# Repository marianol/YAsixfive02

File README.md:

# YAsixfive02 - Yet another 6502 SBC

Just my own take on a 6502 single board computer, inspired on Garth Wilson's excellent 6502 Primer, Daryl Rictor, Ben Eater, and my own beautiful C=64 and all the classic 8-bit computers of the laste 70s early 80s
This repository contains all the work in progress while I build my own SBC. So far I only have my PCB work here, more to come. 
I got tired of having a rat's nest of wires in breadboards and since I'm no wire-rapper I started with a basic PCB to hold CPU, Memory and ROM with a connector so I can start testing the "extras" like serial, VIA, etc.

Not that this is work in progress.. 

## References and Credits

This is my list of references and places where I have found most of the answers to my questions:

- [Ben Eater](https://eater.net) - his videos inspired me to start playing with electronicas again.
- [Garth Wilson's 6502 Primer](http://wilsonminesco.com/6502primer/) - Kudos sir, you have created the bible of 6502-SBC information.
- [Daryl Rictor](https://sbc.rictor.org/home.html) - great documentation on his projects and infinite wisdom in the 6505.org forum.
- [Grant Searle](http://searle.x10host.com/6502/Simple6502.html) - Great example and information on his simple 8 (or 7) chip 6502 SBC.
- And of course 6502.org, Reddit and all the people that share information that I find with google :)

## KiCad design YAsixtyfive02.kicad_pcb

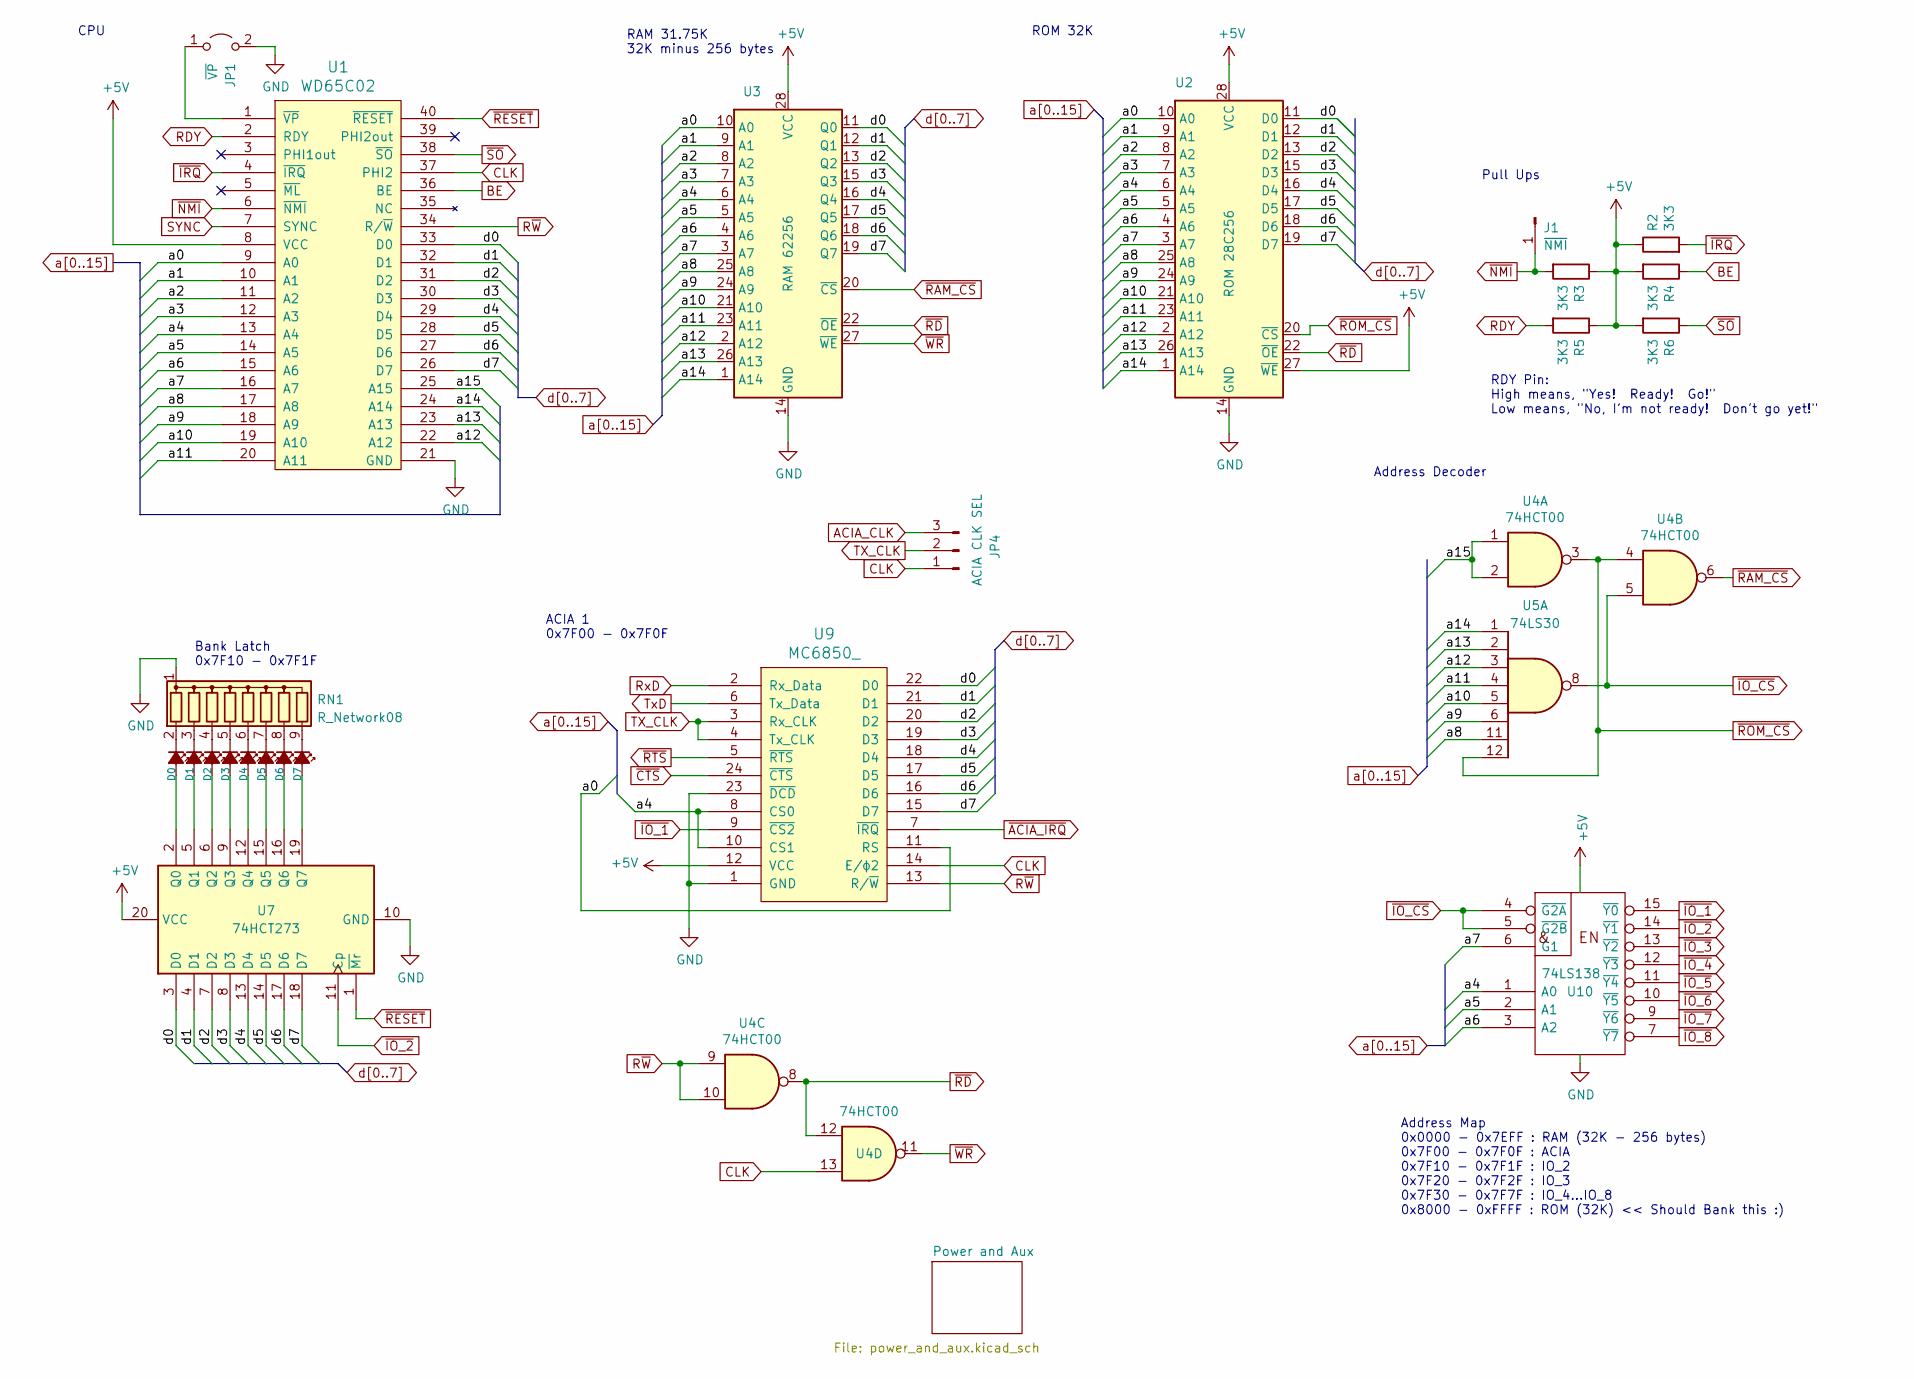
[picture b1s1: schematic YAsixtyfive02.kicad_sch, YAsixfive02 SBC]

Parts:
D0: CTL_0; LED_SMALL_3.0mm
D1: CTL_1; LED_SMALL_3.0mm
D2: CTL_2; LED_SMALL_3.0mm
D3, D4, D5, D6, D7: 3; LED_SMALL_3.0mm
J1: ~{NMI}; PinHeader_1x01_P2.54mm_Vertical
JP1: ~{VP}; PinHeader_1x02_P2.54mm_Vertical
JP4: ACIA CLK SEL; PinHeader_1x03_P2.54mm_Vertical
R2, R3, R4, R5, R6: 3K3; R_Axial_DIN0207_L6.3mm_D2.5mm_P10.16mm_Horizontal
RN1: R_Network08; R_Array_SIP9
U1: WD65C02; DIP-40_W15.24mm_Socket_LongPads
U2: ROM 28C256; DIP-28_W15.24mm_Socket_LongPads
U3: RAM 62256; DIP-28_W15.24mm_Socket_LongPads
U4: 74HCT00; DIP-14_W7.62mm_Socket_LongPads
U5: 74LS30; DIP-14_W7.62mm_Socket_LongPads
U7: 74HCT273; DIP-20_W7.62mm_Socket_LongPads
U9: MC6850_; DIP-24_W15.24mm_Socket_LongPads
U10: 74LS138; DIP-16_W7.62mm_Socket_LongPads

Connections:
+5V: R2.1, R3.1, R4.2, R5.1, R6.2, U1.8 (VCC), U2.27 (~WE), U2.28 (VCC), U3.28 (VCC), U7.20 (VCC), U9.12 (VCC), U10.16 (VCC); also elsewhere on the board
ACIA_CLK: JP4.3
BE: R4.1, U1.36 (BE)
CLK: JP4.1, U1.37 (PHI2), U4.13, U9.14 (E/ϕ2); also elsewhere on the board
GND: JP1.2 (B), RN1.1 (common), U1.21 (GND), U2.14 (GND), U3.14 (GND), U7.10 (GND), U9.1 (GND), U9.23 (~DCD), U10.8 (GND); also elsewhere on the board
unnamed: D0.1 (K), RN1.2 (R1)
unnamed: D0.2 (A), U7.2 (Q0)
unnamed: D1.1 (K), RN1.3 (R2)
unnamed: D1.2 (A), U7.5 (Q1)
unnamed: D2.1 (K), RN1.4 (R3)
unnamed: D2.2 (A), U7.6 (Q2)
unnamed: D3.1 (K), RN1.5 (R4)
unnamed: D3.2 (A), U7.9 (Q3)
unnamed: D4.1 (K), RN1.6 (R5)
unnamed: D4.2 (A), U7.12 (Q4)
unnamed: D5.1 (K), RN1.7 (R6)
unnamed: D5.2 (A), U7.15 (Q5)
unnamed: D6.1 (K), RN1.8 (R7)
unnamed: D6.2 (A), U7.16 (Q6)
unnamed: D7.1 (K), RN1.9 (R8)
unnamed: D7.2 (A), U7.19 (Q7)
unnamed: JP1.1 (A), U1.1 (~VP)
RDY: R5.2, U1.2 (RDY); also elsewhere on the board
RxD: U9.2 (Rx_Data); also elsewhere on the board
R~W: U1.34 (R/~W), U4.9, U4.10, U9.13 (R/~W); also elsewhere on the board
SYNC: U1.7 (SYNC); also elsewhere on the board
TX_CLK: JP4.2, U9.3 (Rx_CLK), U9.4 (Tx_CLK); also elsewhere on the board
TxD: U9.6 (Tx_Data); also elsewhere on the board
a0: U1.9 (A0), U2.10 (A0), U3.10 (A0), U9.11 (RS); also elsewhere on the board
a1: U1.10 (A1), U2.9 (A1), U3.9 (A1); also elsewhere on the board
a2: U1.11 (A2), U2.8 (A2), U3.8 (A2); also elsewhere on the board
a3: U1.12 (A3), U2.7 (A3), U3.7 (A3); also elsewhere on the board
a4: U1.13 (A4), U2.6 (A4), U3.6 (A4), U9.8 (CS0), U9.10 (CS1), U10.1 (A0); also elsewhere on the board
a5: U1.14 (A5), U2.5 (A5), U3.5 (A5), U10.2 (A1); also elsewhere on the board
a6: U1.15 (A6), U2.4 (A6), U3.4 (A6), U10.3 (A2); also elsewhere on the board
a7: U1.16 (A7), U2.3 (A7), U3.3 (A7), U10.6 (G1); also elsewhere on the board
a8: U1.17 (A8), U2.25 (A8), U3.25 (A8), U5.11; also elsewhere on the board
a9: U1.18 (A9), U2.24 (A9), U3.24 (A9), U5.6; also elsewhere on the board
a10: U1.19 (A10), U2.21 (A10), U3.21 (A10), U5.5; also elsewhere on the board
a11: U1.20 (A11), U2.23 (A11), U3.23 (A11), U5.4; also elsewhere on the board
a12: U1.22 (A12), U2.2 (A12), U3.2 (A12), U5.3; also elsewhere on the board
a13: U1.23 (A13), U2.26 (A13), U3.26 (A13), U5.2; also elsewhere on the board
a14: U1.24 (A14), U2.1 (A14), U3.1 (A14), U5.1; also elsewhere on the board
a15: U1.25 (A15), U4.1, U4.2; also elsewhere on the board
d0: U1.33 (D0), U2.11 (D0), U3.11 (Q0), U7.3 (D0), U9.22 (D0); also elsewhere on the board
d1: U1.32 (D1), U2.12 (D1), U3.12 (Q1), U7.4 (D1), U9.21 (D1); also elsewhere on the board
d2: U1.31 (D2), U2.13 (D2), U3.13 (Q2), U7.7 (D2), U9.20 (D2); also elsewhere on the board
d3: U1.30 (D3), U2.15 (D3), U3.15 (Q3), U7.8 (D3), U9.19 (D3); also elsewhere on the board
d4: U1.29 (D4), U2.16 (D4), U3.16 (Q4), U7.13 (D4), U9.18 (D4); also elsewhere on the board
d5: U1.28 (D5), U2.17 (D5), U3.17 (Q5), U7.14 (D5), U9.17 (D5); also elsewhere on the board
d6: U1.27 (D6), U2.18 (D6), U3.18 (Q6), U7.17 (D6), U9.16 (D6); also elsewhere on the board
d7: U1.26 (D7), U2.19 (D7), U3.19 (Q7), U7.18 (D7), U9.15 (D7); also elsewhere on the board
~ACIA_IRQ: U9.7 (~IRQ); also elsewhere on the board
~CTS: U9.24 (~CTS); also elsewhere on the board
~IO_1: U9.9 (~CS2), U10.15 (~Y0)
~IO_2: U7.11 (Cp), U10.14 (~Y1)
~IO_3: U10.13 (~Y2); also elsewhere on the board
~IO_4: U10.12 (~Y3); also elsewhere on the board
~IO_5: U10.11 (~Y4); also elsewhere on the board
~IO_6: U10.10 (~Y5); also elsewhere on the board
~IO_7: U10.9 (~Y6); also elsewhere on the board
~IO_8: U10.7 (~Y7); also elsewhere on the board
~IO_CS: U4.5, U5.8, U10.4 (~G2A), U10.5 (~G2B); also elsewhere on the board
~IRQ: R2.2, U1.4 (~IRQ); also elsewhere on the board
~NMI: J1.1, R3.2, U1.6 (~NMI); also elsewhere on the board
~RAM_CS: U3.20 (~CS), U4.6; also elsewhere on the board
~RD: U2.22 (~OE), U3.22 (~OE), U4.8, U4.12; also elsewhere on the board
~RESET: U1.40 (~RESET), U7.1 (~Mr); also elsewhere on the board
~ROM_CS: U2.20 (~CS), U4.3, U4.4, U5.12; also elsewhere on the board
~RTS: U9.5 (~RTS); also elsewhere on the board
~SO: R6.1, U1.38 (~SO)
~WR: U3.27 (~WE), U4.11; also elsewhere on the board

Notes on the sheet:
CPU
Pull Ups
ROM 32K
RDY Pin: High means, "Yes! Ready! Go!" Low means, "No, I'm not ready! Don't go yet!"
Address Decoder
RAM 31.75K 32K minus 256 bytes
Bank Latch 0x7F10 - 0x7F1F
ACIA 1 0x7F00 - 0x7F0F
Address Map 0x0000 - 0x7EFF : RAM (32K - 256 bytes) 0x7F00 - 0x7F0F : ACIA 0x7F10 - 0x7F1F : IO_2 0x7F20 - 0x7F2F : IO_3 0x7F30 - 0x7F7F : IO_4...IO_8 0x8000 - 0xFFFF : ROM (32K) << Should Bank this :)

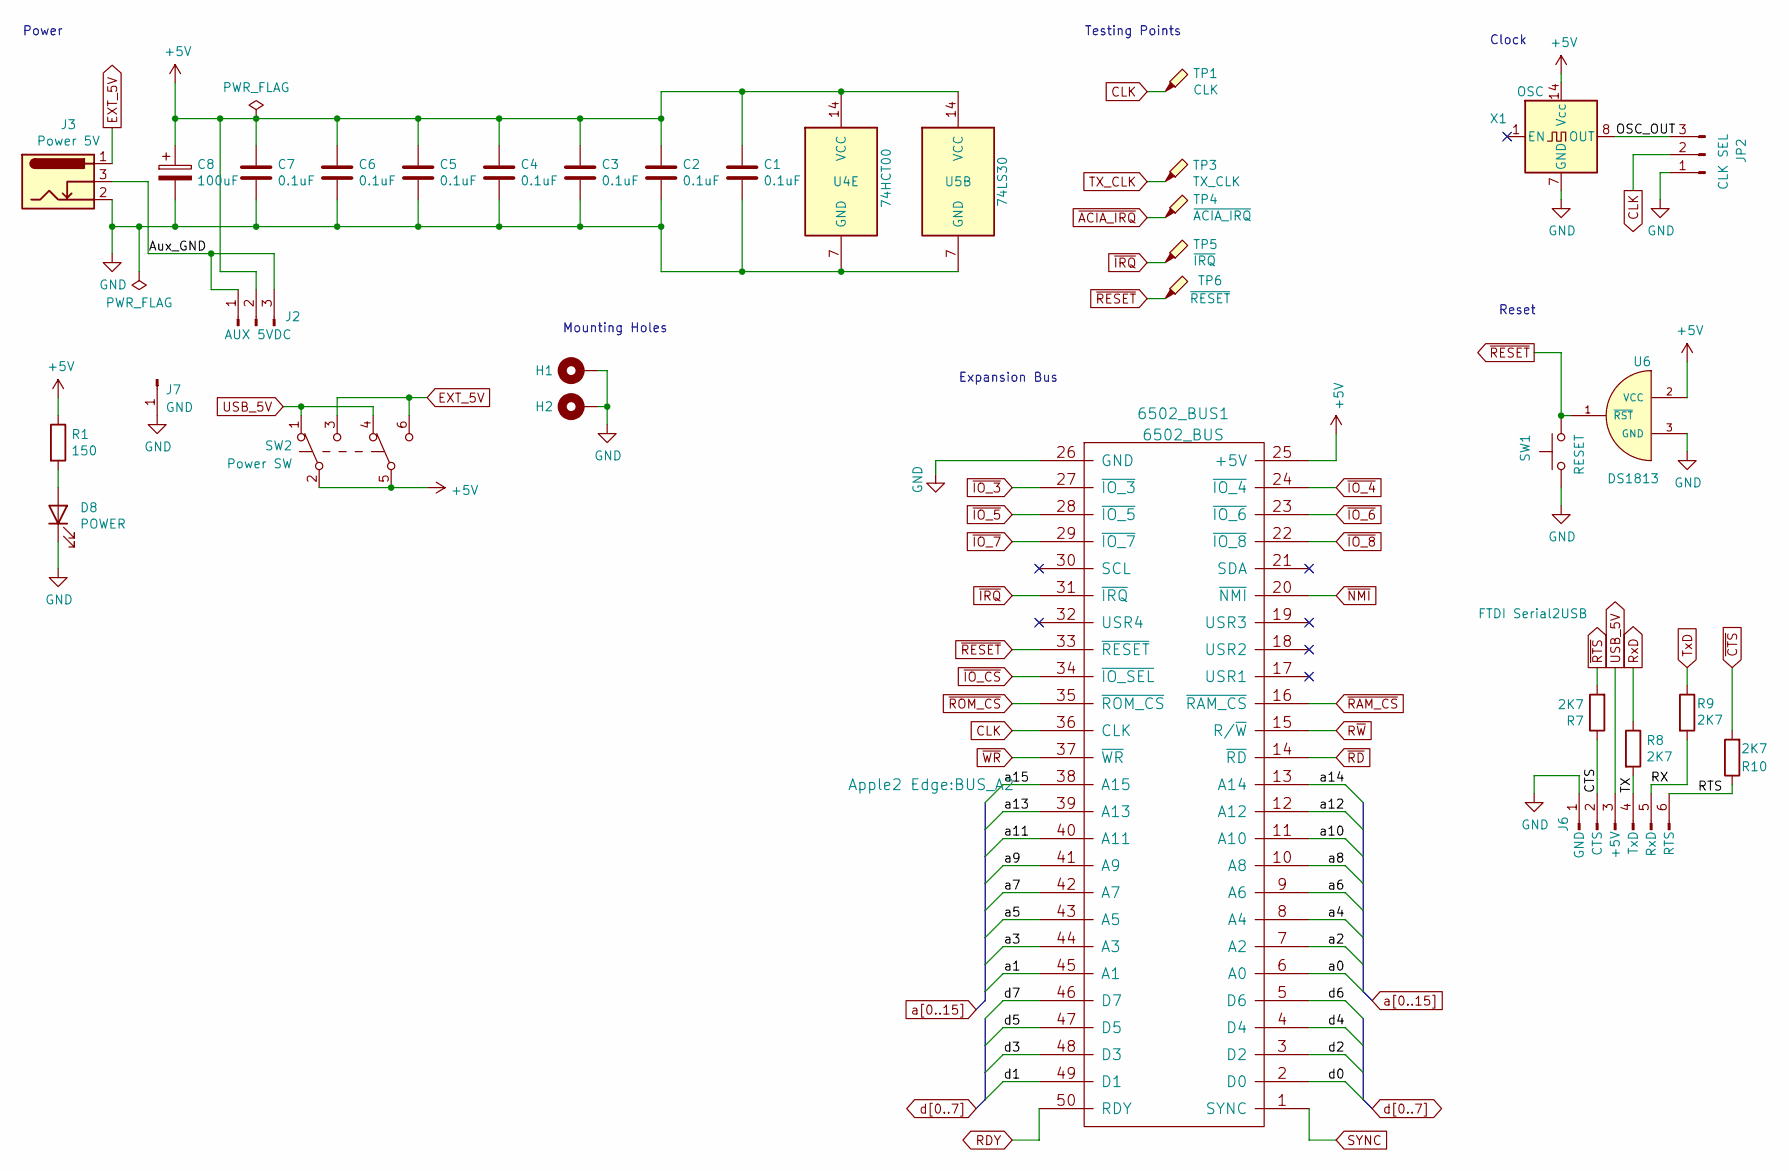
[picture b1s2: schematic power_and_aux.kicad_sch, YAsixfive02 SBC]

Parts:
6502_BUS1: 6502_BUS; BUS_A2
C1, C2, C3, C4, C5, C6, C7: 0.1uF; C_Disc_D4.3mm_W1.9mm_P5.00mm
C8: 100uF; CP_Radial_D6.3mm_P2.50mm
D8: POWER; LED_D3.0mm
H1, H2: MNT; MountingHole_3.2mm_M3_DIN965_Pad_TopBottom
J2: AUX 5VDC; PinHeader_1x03_P2.54mm_Vertical
J3: Power 5V; BarrelJack_Horizontal
J6: FTDI Serial2USB; PinHeader_1x06_P2.54mm_Vertical
J7: GND; PinHeader_1x01_P2.54mm_Vertical
JP2: CLK SEL; PinHeader_1x03_P2.54mm_Vertical
R1: 150; R_Axial_DIN0207_L6.3mm_D2.5mm_P10.16mm_Horizontal
R7, R8, R9, R10: 2K7; R_Axial_DIN0207_L6.3mm_D2.5mm_P10.16mm_Horizontal
SW1: RESET; SW_PUSH_6mm_H5mm
SW2: Power SW; SW_NKK_GW12LJP
TP1: CLK; TestPoint_THTPad_1.0x1.0mm_Drill0.5mm
TP3: TX_CLK; TestPoint_THTPad_1.0x1.0mm_Drill0.5mm
TP4: ~{ACIA_IRQ}; TestPoint_THTPad_1.0x1.0mm_Drill0.5mm
TP5: ~{IRQ}; TestPoint_THTPad_1.0x1.0mm_Drill0.5mm
TP6: ~{RESET}; TestPoint_THTPad_1.0x1.0mm_Drill0.5mm
U4: 74HCT00; DIP-14_W7.62mm_Socket_LongPads
U5: 74LS30; DIP-14_W7.62mm_Socket_LongPads
U6: DS1813; TO-92; MANUFACTURER_PART_NUMBER ds181315+
X1: OSC; Oscillator_DIP-14

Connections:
+5V: 6502_BUS1.25 (+5V), C1.1, C2.1, C3.1, C4.1, C5.1, C6.1, C7.1, C8.1, J2.2, R1.1, SW2.2 (B), SW2.5 (B), U4.14 (VCC), U5.14 (VCC), U6.2 (VCC), X1.14 (Vcc); also elsewhere on the board
/Power and Aux/Aux_GND: J2.1, J2.3, J3.3
/Power and Aux/CTS: J6.2 (CTS), R7.1
/Power and Aux/OSC_OUT: JP2.3, X1.8 (OUT)
/Power and Aux/RTS: J6.6 (RTS), R10.1
/Power and Aux/RX: J6.5 (RxD), R9.2
/Power and Aux/TX: J6.4 (TxD), R8.2
CLK: 6502_BUS1.36 (CLK), JP2.2, TP1.1; also elsewhere on the board
EXT_5V: J3.1, SW2.3 (C), SW2.6 (C)
GND: 6502_BUS1.26 (GND), C1.2, C2.2, C3.2, C4.2, C5.2, C6.2, C7.2, C8.2, D8.1 (K), H1.1, H2.1, J3.2, J6.1 (GND), J7.1, JP2.1, SW1.1, U4.7 (GND), U5.7 (GND), U6.3 (GND), X1.7 (GND); also elsewhere on the board
unnamed: D8.2 (A), R1.2
RDY: 6502_BUS1.50 (RDY); also elsewhere on the board
RxD: R8.1; also elsewhere on the board
R~W: 6502_BUS1.15 (R/~W); also elsewhere on the board
SYNC: 6502_BUS1.1 (SYNC); also elsewhere on the board
TX_CLK: TP3.1; also elsewhere on the board
TxD: R9.1; also elsewhere on the board
USB_5V: J6.3 (+5V), SW2.1 (A), SW2.4 (A)
a0: 6502_BUS1.6 (A0); also elsewhere on the board
a1: 6502_BUS1.45 (A1); also elsewhere on the board
a2: 6502_BUS1.7 (A2); also elsewhere on the board
a3: 6502_BUS1.44 (A3); also elsewhere on the board
a4: 6502_BUS1.8 (A4); also elsewhere on the board
a5: 6502_BUS1.43 (A5); also elsewhere on the board
a6: 6502_BUS1.9 (A6); also elsewhere on the board
a7: 6502_BUS1.42 (A7); also elsewhere on the board
a8: 6502_BUS1.10 (A8); also elsewhere on the board
a9: 6502_BUS1.41 (A9); also elsewhere on the board
a10: 6502_BUS1.11 (A10); also elsewhere on the board
a11: 6502_BUS1.40 (A11); also elsewhere on the board
a12: 6502_BUS1.12 (A12); also elsewhere on the board
a13: 6502_BUS1.39 (A13); also elsewhere on the board
a14: 6502_BUS1.13 (A14); also elsewhere on the board
a15: 6502_BUS1.38 (A15); also elsewhere on the board
d0: 6502_BUS1.2 (D0); also elsewhere on the board
d1: 6502_BUS1.49 (D1); also elsewhere on the board
d2: 6502_BUS1.3 (D2); also elsewhere on the board
d3: 6502_BUS1.48 (D3); also elsewhere on the board
d4: 6502_BUS1.4 (D4); also elsewhere on the board
d5: 6502_BUS1.47 (D5); also elsewhere on the board
d6: 6502_BUS1.5 (D6); also elsewhere on the board
d7: 6502_BUS1.46 (D7); also elsewhere on the board
~ACIA_IRQ: TP4.1; also elsewhere on the board
~CTS: R10.2; also elsewhere on the board
~IO_3: 6502_BUS1.27 (~IO_3); also elsewhere on the board
~IO_4: 6502_BUS1.24 (~IO_4); also elsewhere on the board
~IO_5: 6502_BUS1.28 (~IO_5); also elsewhere on the board
~IO_6: 6502_BUS1.23 (~IO_6); also elsewhere on the board
~IO_7: 6502_BUS1.29 (~IO_7); also elsewhere on the board
~IO_8: 6502_BUS1.22 (~IO_8); also elsewhere on the board
~IO_CS: 6502_BUS1.34 (~IO_SEL); also elsewhere on the board
~IRQ: 6502_BUS1.31 (~IRQ), TP5.1; also elsewhere on the board
~NMI: 6502_BUS1.20 (~NMI); also elsewhere on the board
~RAM_CS: 6502_BUS1.16 (~RAM_CS); also elsewhere on the board
~RD: 6502_BUS1.14 (~RD); also elsewhere on the board
~RESET: 6502_BUS1.33 (~RESET), SW1.2, TP6.1, U6.1 (~RST); also elsewhere on the board
~ROM_CS: 6502_BUS1.35 (~ROM_CS); also elsewhere on the board
~RTS: R7.2; also elsewhere on the board
~WR: 6502_BUS1.37 (~WR); also elsewhere on the board

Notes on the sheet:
Power
Clock
Expansion Bus
Testing Points
Reset
Mounting Holes

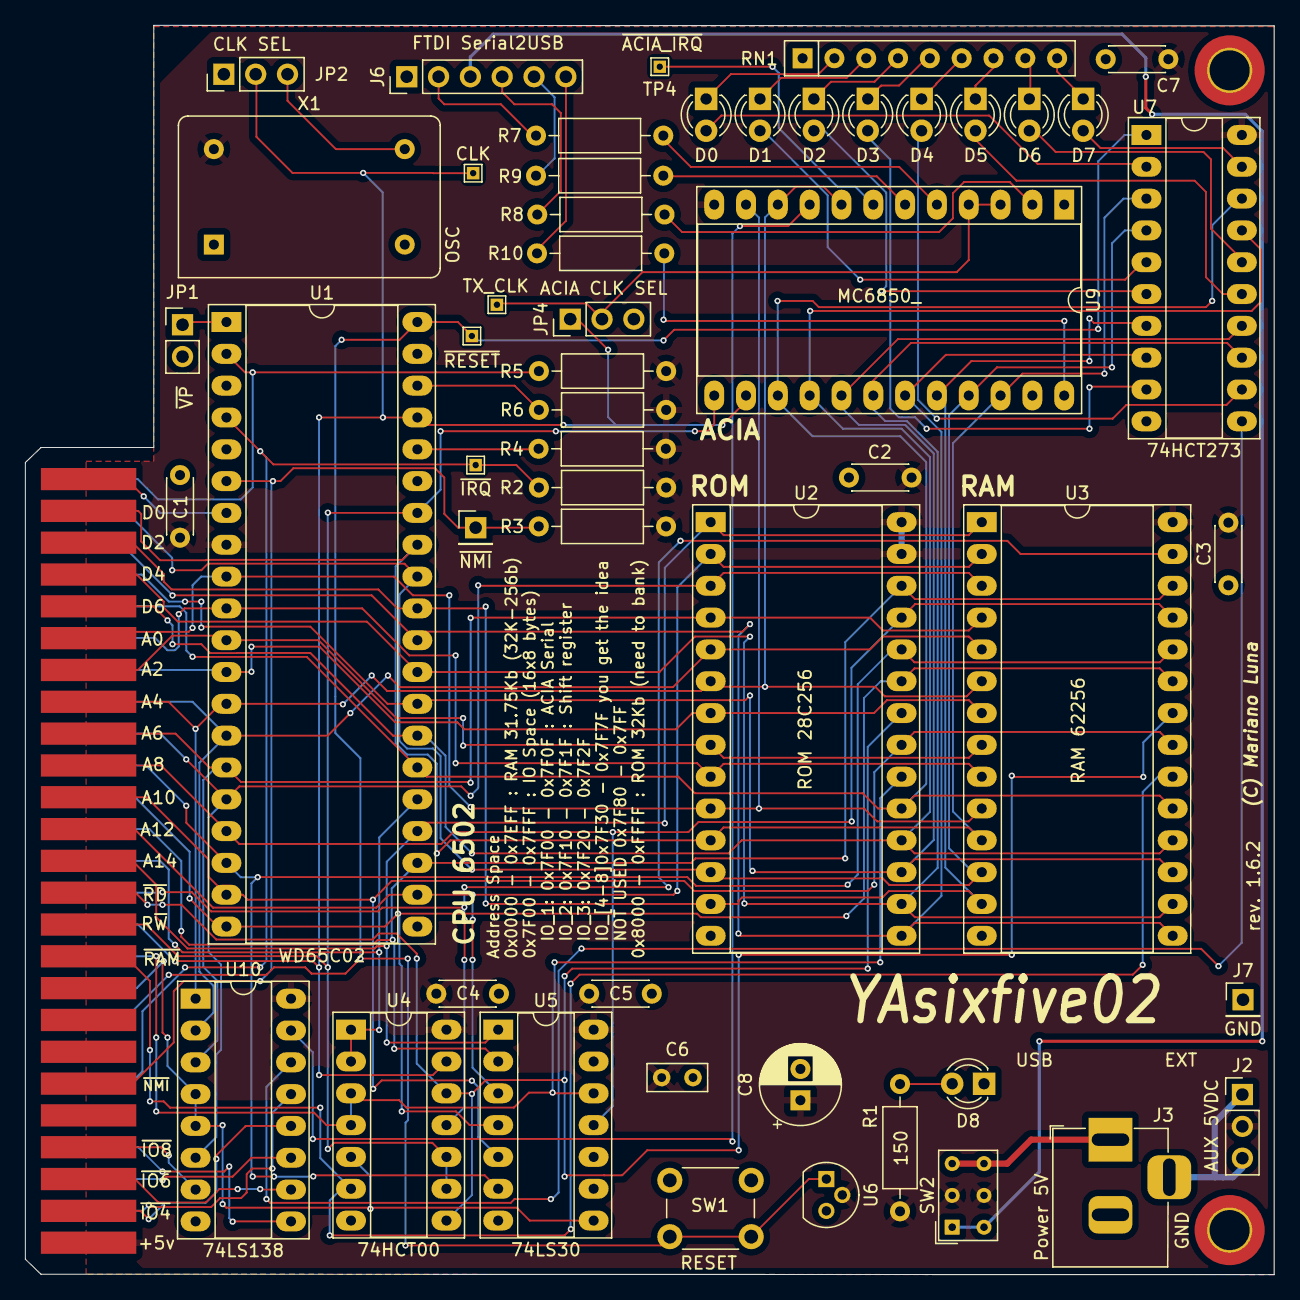
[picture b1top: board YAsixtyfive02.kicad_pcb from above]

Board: 2 copper layers, 99.7 x 99.7 mm, 56 parts (0 on the bottom side), 80 nets.

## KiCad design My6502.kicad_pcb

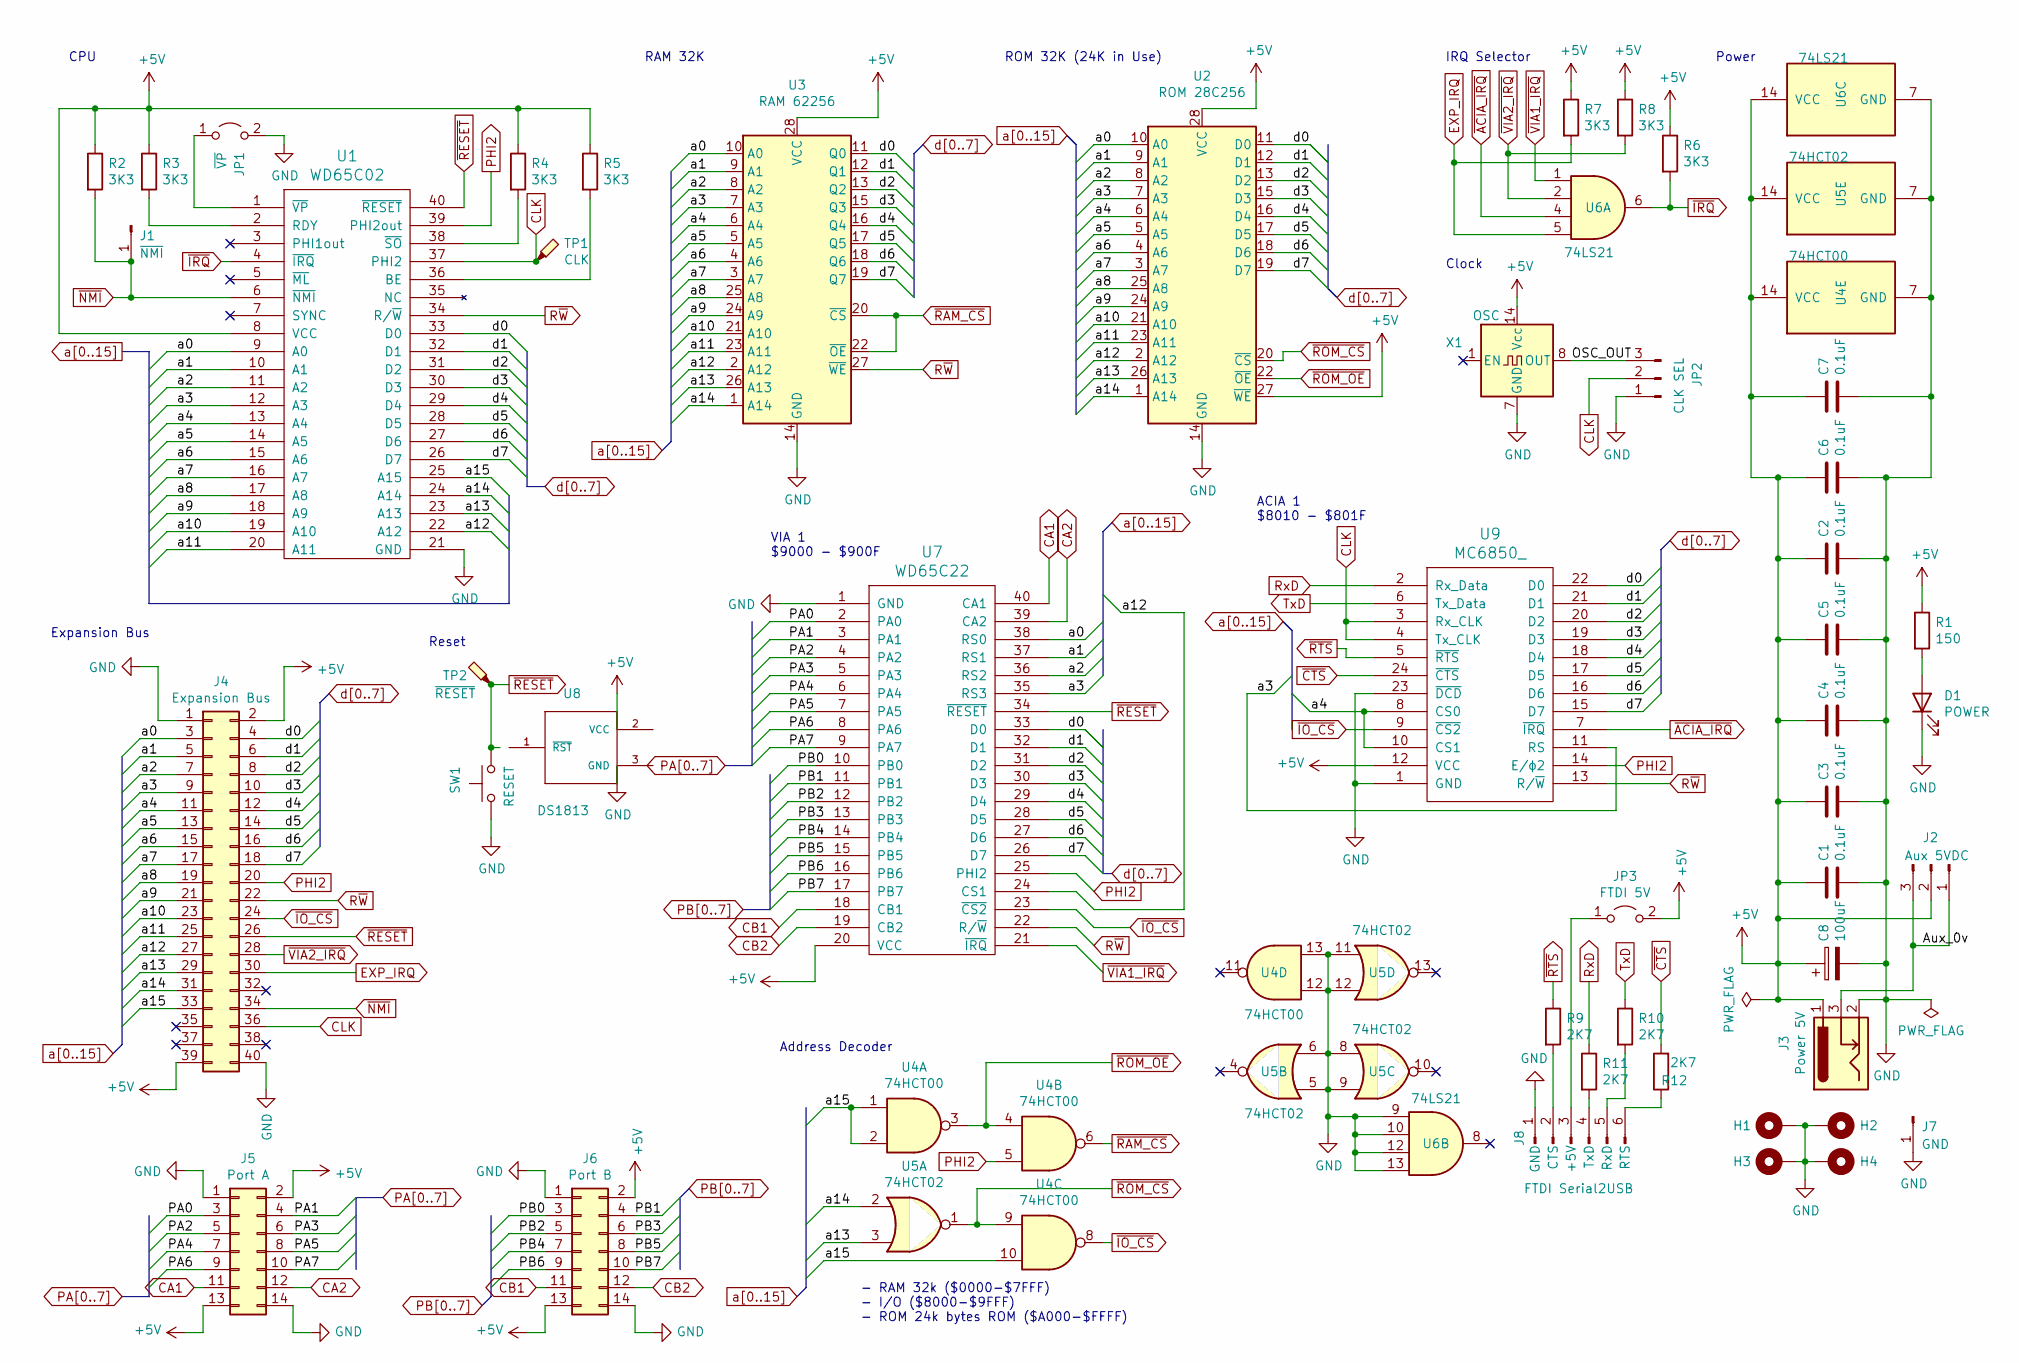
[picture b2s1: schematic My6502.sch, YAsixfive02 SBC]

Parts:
C1, C2, C3, C4, C5, C6, C7: 0.1uF; C_Disc_D4.3mm_W1.9mm_P5.00mm
C8: 100uF; CP_Radial_D8.0mm_P3.80mm
D1: POWER; LED_D3.0mm
H1, H2, H3, H4: MNT; MountingHole_3.2mm_M3_DIN965_Pad_TopBottom
J1: ~NMI; PinHeader_1x01_P2.54mm_Vertical
J2: Aux 5VDC; PinHeader_1x03_P2.54mm_Vertical
J3: Power 5V; BarrelJack_Horizontal
J4: Expansion Bus; PinSocket_2x20_P2.54mm_Vertical
J5: Port A; PinSocket_2x07_P2.54mm_Vertical
J6: Port B; PinSocket_2x07_P2.54mm_Vertical
J7: GND; PinHeader_1x01_P2.54mm_Vertical
J8: FTDI Serial2USB; PinHeader_1x06_P2.54mm_Vertical
JP1: ~VP; PinHeader_1x02_P2.54mm_Vertical
JP2: CLK SEL; PinHeader_1x03_P2.54mm_Vertical
JP3: FTDI 5V; PinHeader_2x01_P2.54mm_Vertical
R1: 150; R_Axial_DIN0207_L6.3mm_D2.5mm_P10.16mm_Horizontal
R2, R3, R4, R5, R6, R7, R8: 3K3; R_Axial_DIN0207_L6.3mm_D2.5mm_P10.16mm_Horizontal
R9, R10, R11, R12: 2K7; R_Axial_DIN0207_L6.3mm_D2.5mm_P10.16mm_Horizontal
SW1: RESET; SW_PUSH_6mm_H5mm
TP1: CLK; TestPoint_THTPad_2.0x2.0mm_Drill1.0mm
TP2: ~RESET; TestPoint_THTPad_2.0x2.0mm_Drill1.0mm
U1: WD65C02; DIP-40_W15.24mm_Socket_LongPads
U2: ROM 28C256; DIP-28_W15.24mm_Socket_LongPads
U3: RAM 62256; DIP-28_W15.24mm_Socket_LongPads
U4: 74HCT00; DIP-14_W7.62mm_Socket_LongPads
U5: 74HCT02; DIP-14_W7.62mm_Socket_LongPads
U6: 74LS21; DIP-14_W7.62mm_Socket_LongPads
U7: WD65C22; DIP-40_W15.24mm_Socket_LongPads
U8: DS1813; TO-92; MANUFACTURER_PART_NUMBER ds181315+
U9: MC6850_; DIP-24_W15.24mm_LongPads
X1: OSC; Oscillator_DIP-14

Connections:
+5V: C1.1, C2.1, C3.1, C4.1, C5.1, C6.1, C7.1, C8.1, J2.2, J3.1, J4.2, J4.39, J5.2, J5.13, J6.2, J6.13, JP3.2 (B), R1.1, R2.1, R3.1, R4.1, R5.1, R6.1, R7.1, R8.1, U1.8 (VCC), U2.27 (~WE), U2.28 (VCC), U3.28 (VCC), U4.14 (VCC), U5.14 (VCC), U6.14 (VCC), U7.20 (VCC), U8.2 (VCC), U9.12 (VCC), X1.14 (Vcc)
/Aux_0v: J2.1, J2.3, J3.3
/OSC_OUT: JP2.3, X1.8 (OUT)
CA1: J5.11, U7.40 (CA1)
CA2: J5.12, U7.39 (CA2)
CB1: J6.11, U7.18 (CB1)
CB2: J6.12, U7.19 (CB2)
CLK: J4.36, JP2.2, TP1.1, U1.37 (PHI2), U9.3 (Rx_CLK), U9.4 (Tx_CLK)
EXP_IRQ: J4.30, R7.2, U6.5
GND: C1.2, C2.2, C3.2, C4.2, C5.2, C6.2, C7.2, C8.2, D1.1 (K), H1.1, H2.1, H3.1, H4.1, J3.2, J4.1, J4.40, J5.1, J5.14, J6.1, J6.14, J7.1, J8.1 (GND), JP1.2 (B), JP2.1, SW1.1, U1.21 (GND), U2.14 (GND), U3.14 (GND), U4.7 (GND), U4.12, U4.13, U5.5, U5.6, U5.7 (GND), U5.8, U5.9, U5.11, U5.12, U6.7 (GND), U6.9, U6.10, U6.12, U6.13, U7.1 (GND), U8.3 (GND), U9.1 (GND), U9.23 (~DCD), X1.7 (GND)
unnamed: D1.2 (A), R1.2
unnamed: J8.2 (CTS), R9.2
unnamed: J8.3 (+5V), JP3.1 (A)
unnamed: J8.4 (TxD), R11.2
unnamed: J8.5 (RxD), R10.2
unnamed: J8.6 (RTS), R12.1
unnamed: JP1.1 (A), U1.1 (~VP)
unnamed: R3.2, U1.2 (RDY)
unnamed: R4.2, U1.38 (~SO)
unnamed: R5.2, U1.36 (BE)
PA0: J5.3, U7.2 (PA0)
PA1: J5.4, U7.3 (PA1)
PA2: J5.5, U7.4 (PA2)
PA3: J5.6, U7.5 (PA3)
PA4: J5.7, U7.6 (PA4)
PA5: J5.8, U7.7 (PA5)
PA6: J5.9, U7.8 (PA6)
PA7: J5.10, U7.9 (PA7)
PB0: J6.3, U7.10 (PB0)
PB1: J6.4, U7.11 (PB1)
PB2: J6.5, U7.12 (PB2)
PB3: J6.6, U7.13 (PB3)
PB4: J6.7, U7.14 (PB4)
PB5: J6.8, U7.15 (PB5)
PB6: J6.9, U7.16 (PB6)
PB7: J6.10, U7.17 (PB7)
PHI2: J4.20, U1.39 (PHI2out), U4.5, U7.25 (PHI2), U9.14 (E/ϕ2)
RxD: R11.1, U9.2 (Rx_Data)
R~W: J4.22, U1.34 (R/~W), U3.27 (~WE), U7.22 (R/~W), U9.13 (R/~W)
TxD: R10.1, U9.6 (Tx_Data)
a0: J4.3, U1.9 (A0), U2.10 (A0), U3.10 (A0), U7.38 (RS0)
a1: J4.5, U1.10 (A1), U2.9 (A1), U3.9 (A1), U7.37 (RS1)
a2: J4.7, U1.11 (A2), U2.8 (A2), U3.8 (A2), U7.36 (RS2)
a3: J4.9, U1.12 (A3), U2.7 (A3), U3.7 (A3), U7.35 (RS3), U9.11 (RS)
a4: J4.11, U1.13 (A4), U2.6 (A4), U3.6 (A4), U9.8 (CS0), U9.10 (CS1)
a5: J4.13, U1.14 (A5), U2.5 (A5), U3.5 (A5)
a6: J4.15, U1.15 (A6), U2.4 (A6), U3.4 (A6)
a7: J4.17, U1.16 (A7), U2.3 (A7), U3.3 (A7)
a8: J4.19, U1.17 (A8), U2.25 (A8), U3.25 (A8)
a9: J4.21, U1.18 (A9), U2.24 (A9), U3.24 (A9)
a10: J4.23, U1.19 (A10), U2.21 (A10), U3.21 (A10)
a11: J4.25, U1.20 (A11), U2.23 (A11), U3.23 (A11)
a12: J4.27, U1.22 (A12), U2.2 (A12), U3.2 (A12), U7.24 (CS1)
a13: J4.29, U1.23 (A13), U2.26 (A13), U3.26 (A13), U5.3
a14: J4.31, U1.24 (A14), U2.1 (A14), U3.1 (A14), U5.2
a15: J4.33, U1.25 (A15), U4.1, U4.2, U4.10
d0: J4.4, U1.33 (D0), U2.11 (D0), U3.11 (Q0), U7.33 (D0), U9.22 (D0)
d1: J4.6, U1.32 (D1), U2.12 (D1), U3.12 (Q1), U7.32 (D1), U9.21 (D1)
d2: J4.8, U1.31 (D2), U2.13 (D2), U3.13 (Q2), U7.31 (D2), U9.20 (D2)
d3: J4.10, U1.30 (D3), U2.15 (D3), U3.15 (Q3), U7.30 (D3), U9.19 (D3)
d4: J4.12, U1.29 (D4), U2.16 (D4), U3.16 (Q4), U7.29 (D4), U9.18 (D4)
d5: J4.14, U1.28 (D5), U2.17 (D5), U3.17 (Q5), U7.28 (D5), U9.17 (D5)
d6: J4.16, U1.27 (D6), U2.18 (D6), U3.18 (Q6), U7.27 (D6), U9.16 (D6)
d7: J4.18, U1.26 (D7), U2.19 (D7), U3.19 (Q7), U7.26 (D7), U9.15 (D7)
~ACIA_IRQ: U6.4, U9.7 (~IRQ)
~CTS: R12.2, U9.24 (~CTS)
~IO_CS: J4.24, U4.8, U7.23 (~CS2), U9.9 (~CS2)
~IRQ: R6.2, U1.4 (~IRQ), U6.6
~NMI: J1.1, J4.34, R2.2, U1.6 (~NMI)
~RAM_CS: U3.20 (~CS), U3.22 (~OE), U4.6
~RESET: J4.26, SW1.2, TP2.1, U1.40 (~RESET), U7.34 (~RESET), U8.1 (~RST)
~ROM_CS: U2.20 (~CS), U4.9, U5.1
~ROM_OE: U2.22 (~OE), U4.3, U4.4
~RTS: R9.1, U9.5 (~RTS)
~VIA1_IRQ: U6.1, U7.21 (~IRQ)
~VIA2_IRQ: J4.28, R8.2, U6.2

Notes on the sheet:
Reset
Power
Clock
IRQ Selector
Address Decoder
CPU
Expansion Bus
RAM 32K
ROM 32K (24K in Use)
- RAM 32k ($0000-$7FFF) - I/O ($8000-$9FFF) - ROM 24k bytes ROM ($A000-$FFFF)
VIA 1 $9000 - $900F
ACIA 1 $8010 - $801F

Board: 2 copper layers, 49 parts (0 on the bottom side), 76 nets, no tracks yet.

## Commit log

2022-09-06 My6502 initial commit, full project witrh big board
2022-09-06 pcb with a 10x10 board`
2022-09-06 10 by 10 finished, gerber output ready
2022-09-06 correct board size to 99.69x99.69
2022-09-06 Gerber Plot foles with new size
2022-09-06 gerber zip redy to send
2022-09-06 PCB Sent to manufacturing
2022-09-06 Preparing for Bus
2022-09-08 Edge board completed and routed
2022-09-12 moving to a backplane
2022-09-12 Clean processor board schematic
2022-09-12 PCB completed CPU Board no clock
2022-09-12 Rev 1 with silkscreen
2022-09-27 Update My6502.pro
    Printing Schematic, need to change 6502 footprint
2022-10-07 New Design with VIA1 on board - WIP
2022-10-07 Added power LED
2022-10-07 Components Placed - missing wiring the VIA
2022-10-07 PCB done minus VIA Registers - DRC Passing
2022-10-07 V1.5 Ready - Full board CPU,RAM,ROM,VIA
2022-10-07 Gerber files and Pictures v 1.5
2022-10-07 Zipped Gerber added
2022-10-08 Gerber file deleted had errors. New Schematic with power leads and GND Test
2022-10-08 YAsicfive02 1.5 final version - Gerber file done
2022-10-10 added fp-info-cache to git ignore
2022-10-10 v1.5 complete with routed PCB.
2022-10-11 Added ACIA in schematic
2022-10-11 c1.5.2 schematic finished - error in U9 oin 23
2022-10-11 Schema ready v1.5.2 ACIA and VIA on
2022-10-11 PCB Component placement first take
2022-10-11 spring cleanning
2022-10-11 new more comprehensive gitignore
2022-10-11 Remove ignored files
2022-10-11 More robust gitignore
2022-10-11 Updated to KiCad 6
2022-10-12 PCB take 1 v1.5.2 Complete VIA + ACIA
2022-10-12 Board cleanup, renders and add backups to gitignore
2022-10-12 deleted old v5 files
2022-10-12 Created README.md
2022-10-12 adding schematic pdf - for real now
2022-10-19 changed PHI2 out to CLK and PCB tweaks
2022-10-21 Simplified board for backplane only CPU/RAM/ROM/ACIA/Glue
2022-10-21 copy of SCH with VIA/ACIA and glue
2022-10-21 Schematic annotated and ERC pass
2022-10-21 Deleted unused gate, ERC passed
2022-10-21 Test Pads Footprint Changed
2022-10-21 COmponents placed ready to route
2022-10-21 PCB Almost ready missing USB Power override
2022-10-21 PCB Completed CPU/ACIA/RAM/ROM
2022-10-21 Updated to a more efficient memory map
    Address Map
    0x0000 - 0x7EFF : RAM (32K - 256 bytes)
    0x7F00 - 0x7F0F : ACIA
    0x7F10 - 0x7F1F : IO_2
    0x7F20 - 0x7F2F : IO_3
    0x7F30 - 0x7F7F : IO_4...IO_8
2022-10-21 rev 1.6.0 ready new memory map
    CPU/ROM/RAM/ACIA/SR New memory map, io in expansion port
2022-10-22 Clean up and minor PCB tweaks
2022-10-24 monor routing revision clean DRC
2022-10-25 rev. 1.6.1 minor pcb routing tweaks all IO in the connector
2022-10-25 rev 1.6.1 ready. minor routing updates and acia CS fixed.
2022-11-03 rev 1.6.1 ready. minor routing updates and acia CS fixed
2022-11-04 added 6502 bus symbol and footprint
2022-11-04 cleaned up schematic
2022-11-04 Schematic re-organized
2022-11-05 Schematic and PCB Updated
2022-11-05 Added 6502 bus to schematic
2022-11-05 6502 Bus Edge Connector done
